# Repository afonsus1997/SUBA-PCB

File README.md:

#SUBA PCB

##O Fantástico circuito do SUBA adaptado a uma PCB! Nunca visto!

###A PCB

###O circuito

###Preparação

###Etched

###Assembled

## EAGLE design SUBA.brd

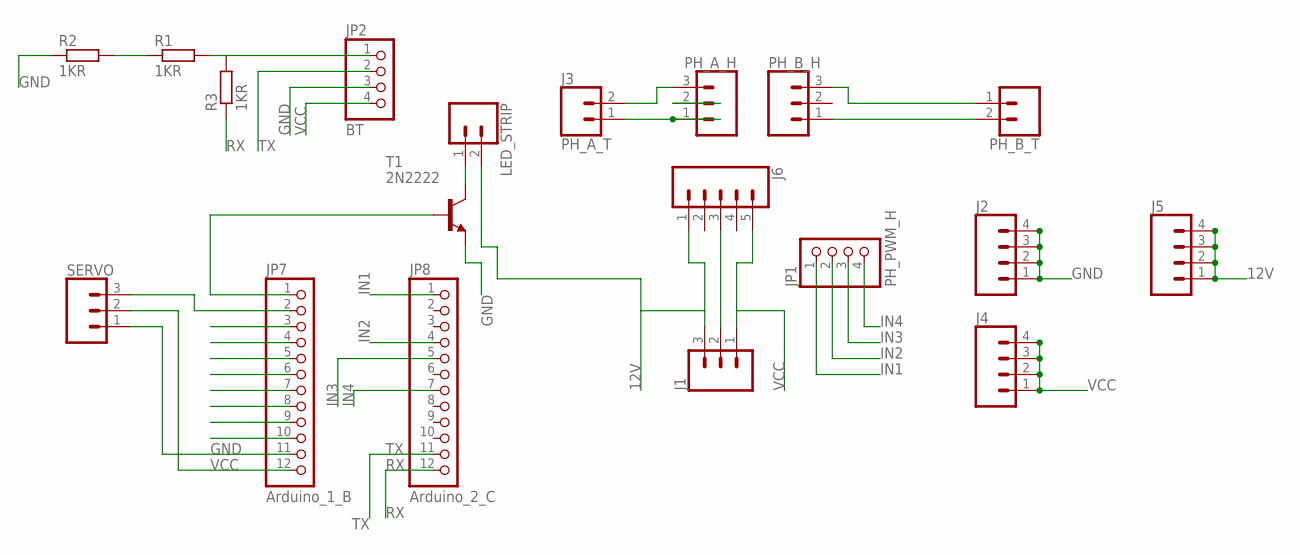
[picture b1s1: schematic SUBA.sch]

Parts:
J1: CONN_03-SCREW-5MM; SCREWTERMINAL-5MM-3
J2, J4, J5: CONN_04; 1X04
J3: PH_A_T; SCREWTERMINAL-5MM-2
J6: CONN_05; 1X05
JP1: PH_PWM_H; 1X04
JP2: BT; 1X04
JP7: Arduino_1_B; 1X12
JP8: Arduino_2_C; 1X12
LED_STRIP: CONN_02; 1X02
PH_A_H: CONN_03; 1X03
PH_B_H: CONN_03; 1X03
PH_B_T: CONN_025MM; SCREWTERMINAL-5MM-2
R1, R2, R3: 1KR; 0204/7
SERVO: CONN_03; 1X03
T1: 2N2222; TO92-EBC-OVAL

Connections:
12V: J1.3, J5.1, J5.2, J5.3, J5.4, J6.1, LED_STRIP.2
GND: J1.2, J2.1, J2.2, J2.3, J2.4, J6.3, JP2.3, JP7.11, R2.1, SERVO.1, T1.E
IN1: JP1.1, JP8.1
IN2: JP1.2, JP8.4
IN3: JP1.3, JP8.5
IN4: JP1.4, JP8.7
unnamed: JP7.1, T1.B
unnamed: J3.2, PH_A_H.3
unnamed: J3.1, PH_A_H.1
unnamed: PH_B_H.3, PH_B_T.1
unnamed: PH_B_H.1, PH_B_T.2
unnamed: R1.1, R2.2
unnamed: JP2.1, R1.2, R3.2
unnamed: JP7.2, SERVO.3
unnamed: LED_STRIP.1, T1.C
RX: JP8.12, R3.1
TX: JP2.2, JP8.11
VCC: J1.1, J4.1, J4.2, J4.3, J4.4, J6.5, JP2.4, JP7.9, JP7.12, SERVO.2

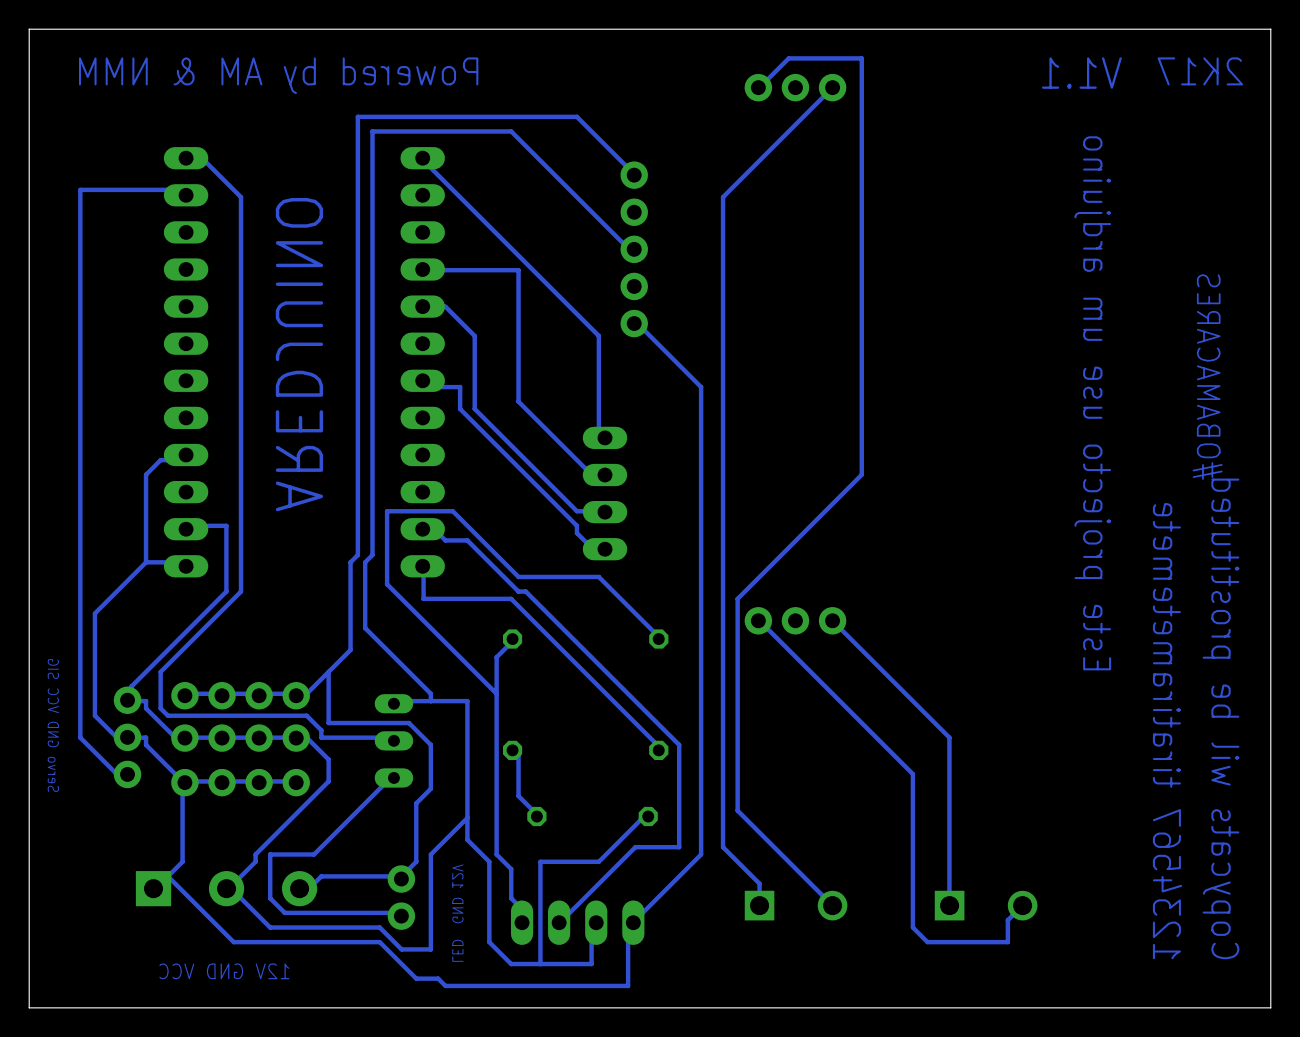
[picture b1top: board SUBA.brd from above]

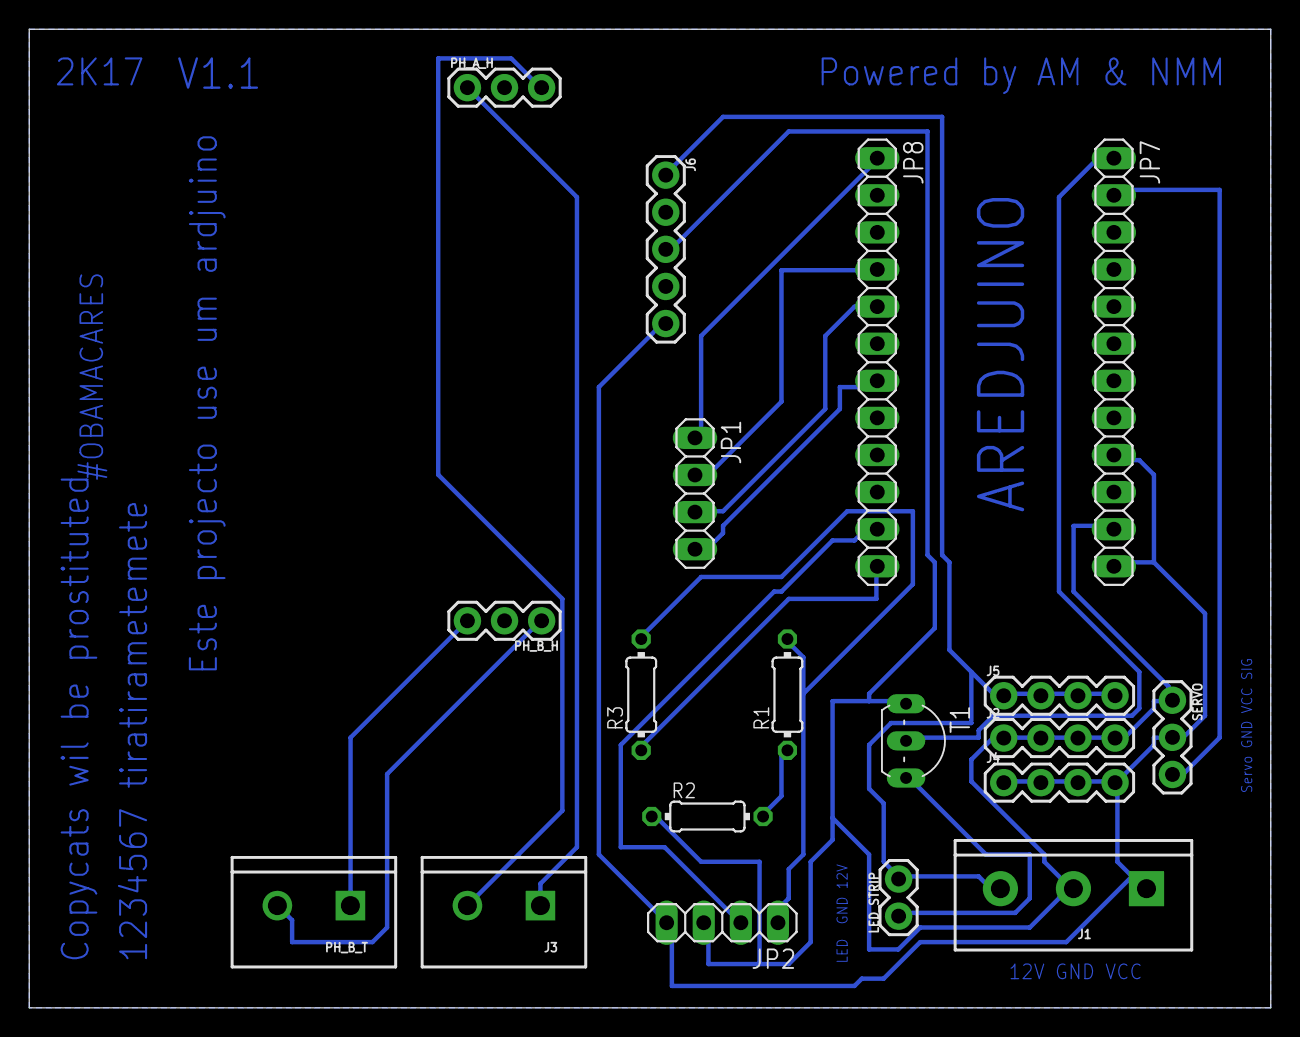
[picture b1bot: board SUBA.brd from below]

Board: 2 copper layers, 85.0 x 67.0 mm, 19 parts (19 on the bottom side), 18 nets.

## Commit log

2017-02-08 isto ja crashou uma vez caralho
2017-02-08 commit 2
2017-02-08 Algumas alterações PCB
2017-02-08 SAFE
2017-02-08 Placed Unrouted
    Placed all components, no routing
2017-02-08 Placed Unrouted2
2017-02-08 100%Routed
    WOOO!
2017-02-08 100% Routed, more spacing
2017-02-08 Added info and pictures to the README.md
2017-02-08 Minor changes to the README.md
2017-02-17 FINAL PCB & Manufacture
2017-02-17 Uploaded pictures & added to readme
2017-02-17 fixed readme

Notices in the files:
parts and their libraries:
SparkFun-Connectors: Licensing: Creative Commons ShareAlike 4.0 International - https://creativecommons.org/licenses/by-sa/4.0
